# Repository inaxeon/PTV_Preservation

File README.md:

# Philips Professional Television test equipment preservation

This repository contains all of the catalogues, manuals and code dumps I have for Philips "PTV" test equipment. Presently that includes:

* PM5534 color pattern generator
* PM5544 color pattern generator
* PM5570 video test signal generator
* PM5580 TV modulator
* PM5588 TV stereo sound modulator (Zweikanalton)
* PM5631 color generator
* PM5638 component color encoder, SPG
* PM5644 color pattern generator
* PM5654 VITS generator & inserter
* PM5655 VITS generator & inserter
* PM5680 TV modulator
* PM5687 TV digital sound modulator (NICAM)
* PM5688 NICAM sound demodulator
* PM5689 NICAM monitor
* PM5690 TV multichannel converter
* PT5XXX series bits and pieces

More will be made available as I find it.

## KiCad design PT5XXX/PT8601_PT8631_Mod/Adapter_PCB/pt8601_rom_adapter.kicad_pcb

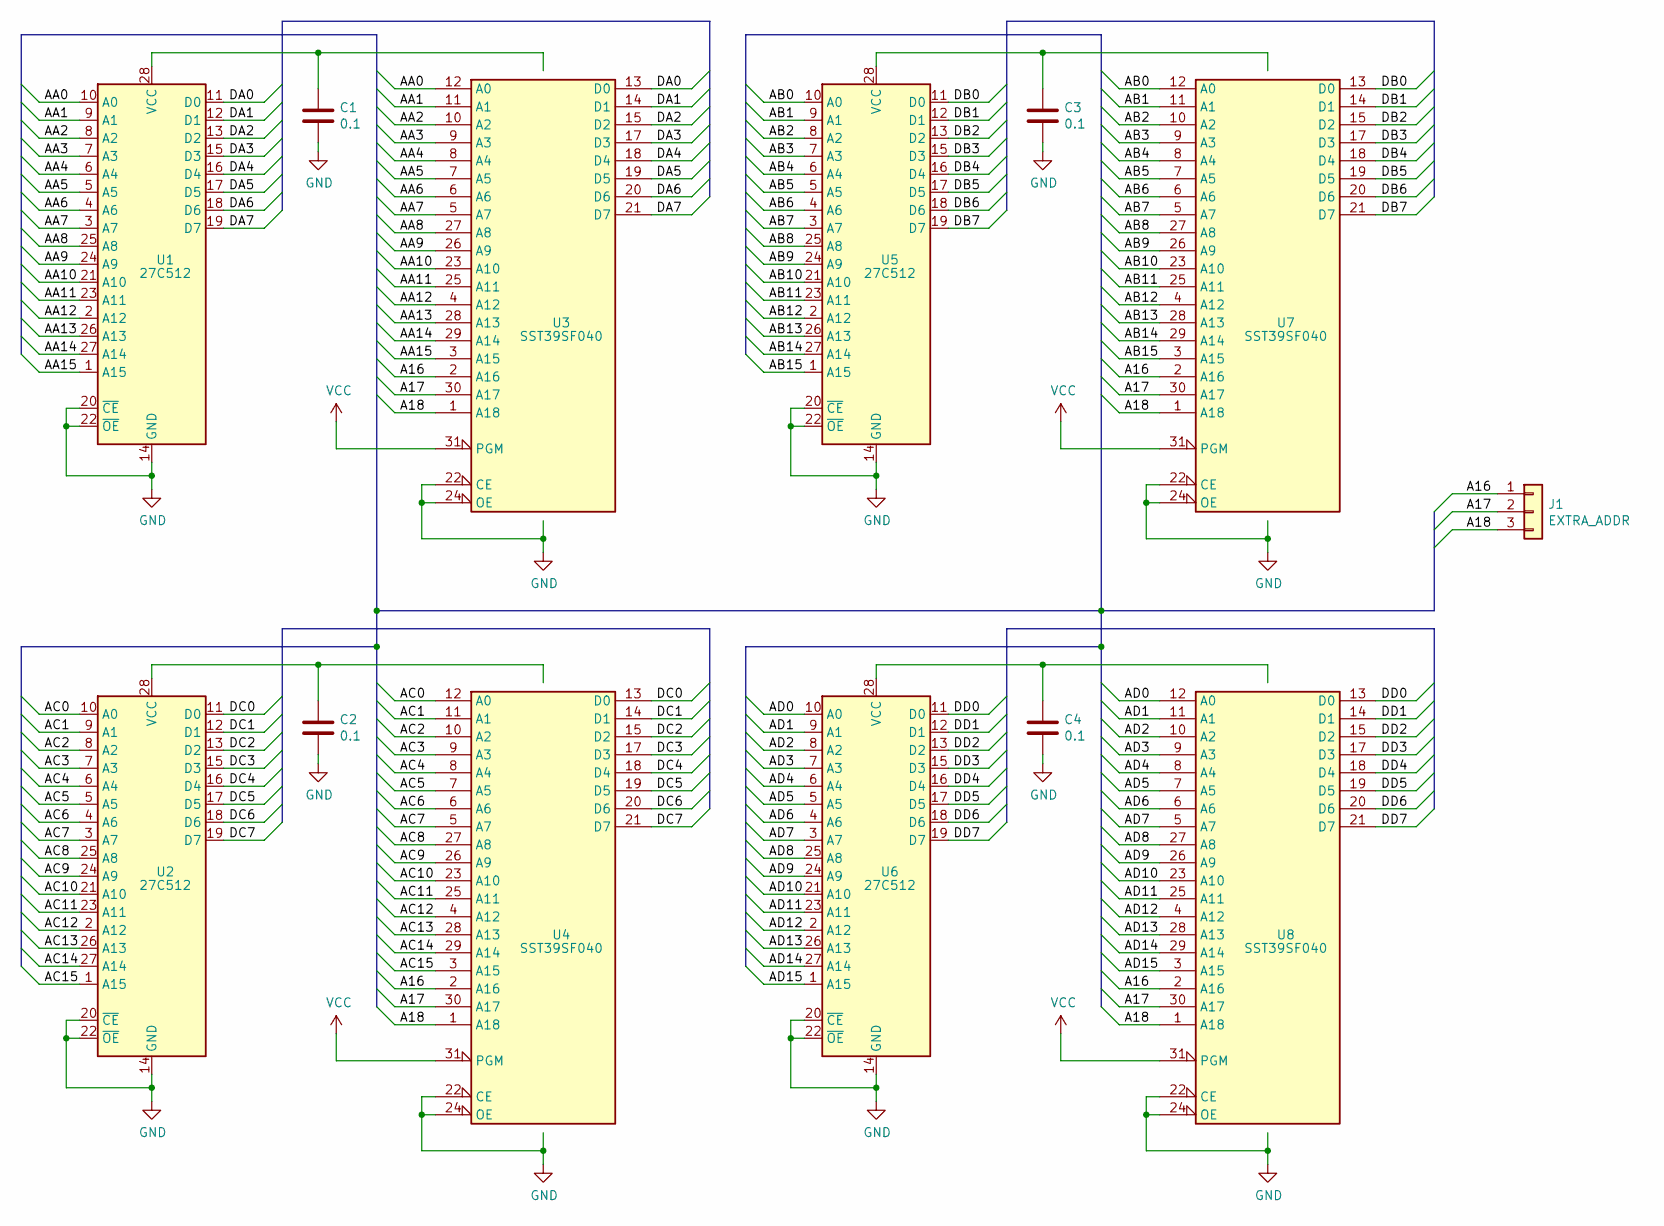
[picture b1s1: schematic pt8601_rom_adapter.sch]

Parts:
C1, C2, C3, C4: 0.1; C_1206_3216Metric
J1: EXTRA_ADDR; PinHeader_1x03_P1.27mm_Vertical
U1, U2, U5, U6: 27C512; DIP-28_W15.24mm
U3, U4, U7, U8: SST39SF040; PLCC_32_SKT

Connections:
/A16: J1.1, U3.2 (A16), U4.2 (A16), U7.2 (A16), U8.2 (A16)
/A17: J1.2, U3.30 (A17), U4.30 (A17), U7.30 (A17), U8.30 (A17)
/A18: J1.3, U3.1 (A18), U4.1 (A18), U7.1 (A18), U8.1 (A18)
/AA0: U1.10 (A0), U3.12 (A0)
/AA1: U1.9 (A1), U3.11 (A1)
/AA2: U1.8 (A2), U3.10 (A2)
/AA3: U1.7 (A3), U3.9 (A3)
/AA4: U1.6 (A4), U3.8 (A4)
/AA5: U1.5 (A5), U3.7 (A5)
/AA6: U1.4 (A6), U3.6 (A6)
/AA7: U1.3 (A7), U3.5 (A7)
/AA8: U1.25 (A8), U3.27 (A8)
/AA9: U1.24 (A9), U3.26 (A9)
/AA10: U1.21 (A10), U3.23 (A10)
/AA11: U1.23 (A11), U3.25 (A11)
/AA12: U1.2 (A12), U3.4 (A12)
/AA13: U1.26 (A13), U3.28 (A13)
/AA14: U1.27 (A14), U3.29 (A14)
/AA15: U1.1 (A15), U3.3 (A15)
/AB0: U5.10 (A0), U7.12 (A0)
/AB1: U5.9 (A1), U7.11 (A1)
/AB2: U5.8 (A2), U7.10 (A2)
/AB3: U5.7 (A3), U7.9 (A3)
/AB4: U5.6 (A4), U7.8 (A4)
/AB5: U5.5 (A5), U7.7 (A5)
/AB6: U5.4 (A6), U7.6 (A6)
/AB7: U5.3 (A7), U7.5 (A7)
/AB8: U5.25 (A8), U7.27 (A8)
/AB9: U5.24 (A9), U7.26 (A9)
/AB10: U5.21 (A10), U7.23 (A10)
/AB11: U5.23 (A11), U7.25 (A11)
/AB12: U5.2 (A12), U7.4 (A12)
/AB13: U5.26 (A13), U7.28 (A13)
/AB14: U5.27 (A14), U7.29 (A14)
/AB15: U5.1 (A15), U7.3 (A15)
/AC0: U2.10 (A0), U4.12 (A0)
/AC1: U2.9 (A1), U4.11 (A1)
/AC2: U2.8 (A2), U4.10 (A2)
/AC3: U2.7 (A3), U4.9 (A3)
/AC4: U2.6 (A4), U4.8 (A4)
/AC5: U2.5 (A5), U4.7 (A5)
/AC6: U2.4 (A6), U4.6 (A6)
/AC7: U2.3 (A7), U4.5 (A7)
/AC8: U2.25 (A8), U4.27 (A8)
/AC9: U2.24 (A9), U4.26 (A9)
/AC10: U2.21 (A10), U4.23 (A10)
/AC11: U2.23 (A11), U4.25 (A11)
/AC12: U2.2 (A12), U4.4 (A12)
/AC13: U2.26 (A13), U4.28 (A13)
/AC14: U2.27 (A14), U4.29 (A14)
/AC15: U2.1 (A15), U4.3 (A15)
/AD0: U6.10 (A0), U8.12 (A0)
/AD1: U6.9 (A1), U8.11 (A1)
/AD2: U6.8 (A2), U8.10 (A2)
/AD3: U6.7 (A3), U8.9 (A3)
/AD4: U6.6 (A4), U8.8 (A4)
/AD5: U6.5 (A5), U8.7 (A5)
/AD6: U6.4 (A6), U8.6 (A6)
/AD7: U6.3 (A7), U8.5 (A7)
/AD8: U6.25 (A8), U8.27 (A8)
/AD9: U6.24 (A9), U8.26 (A9)
/AD10: U6.21 (A10), U8.23 (A10)
/AD11: U6.23 (A11), U8.25 (A11)
/AD12: U6.2 (A12), U8.4 (A12)
/AD13: U6.26 (A13), U8.28 (A13)
/AD14: U6.27 (A14), U8.29 (A14)
/AD15: U6.1 (A15), U8.3 (A15)
/DA0: U1.11 (D0), U3.13 (D0)
/DA1: U1.12 (D1), U3.14 (D1)
/DA2: U1.13 (D2), U3.15 (D2)
/DA3: U1.15 (D3), U3.17 (D3)
/DA4: U1.16 (D4), U3.18 (D4)
/DA5: U1.17 (D5), U3.19 (D5)
/DA6: U1.18 (D6), U3.20 (D6)
/DA7: U1.19 (D7), U3.21 (D7)
/DB0: U5.11 (D0), U7.13 (D0)
/DB1: U5.12 (D1), U7.14 (D1)
/DB2: U5.13 (D2), U7.15 (D2)
/DB3: U5.15 (D3), U7.17 (D3)
/DB4: U5.16 (D4), U7.18 (D4)
/DB5: U5.17 (D5), U7.19 (D5)
/DB6: U5.18 (D6), U7.20 (D6)
/DB7: U5.19 (D7), U7.21 (D7)
/DC0: U2.11 (D0), U4.13 (D0)
/DC1: U2.12 (D1), U4.14 (D1)
/DC2: U2.13 (D2), U4.15 (D2)
/DC3: U2.15 (D3), U4.17 (D3)
/DC4: U2.16 (D4), U4.18 (D4)
/DC5: U2.17 (D5), U4.19 (D5)
/DC6: U2.18 (D6), U4.20 (D6)
/DC7: U2.19 (D7), U4.21 (D7)
/DD0: U6.11 (D0), U8.13 (D0)
/DD1: U6.12 (D1), U8.14 (D1)
/DD2: U6.13 (D2), U8.15 (D2)
/DD3: U6.15 (D3), U8.17 (D3)
/DD4: U6.16 (D4), U8.18 (D4)
/DD5: U6.17 (D5), U8.19 (D5)
/DD6: U6.18 (D6), U8.20 (D6)
/DD7: U6.19 (D7), U8.21 (D7)
GND: C1.2, C2.2, C3.2, C4.2, U1.14 (GND), U1.20 (~CE), U1.22 (~OE), U2.14 (GND), U2.20 (~CE), U2.22 (~OE), U3.16 (GND), U3.22 (CE), U3.24 (OE), U4.16 (GND), U4.22 (CE), U4.24 (OE), U5.14 (GND), U5.20 (~CE), U5.22 (~OE), U6.14 (GND), U6.20 (~CE), U6.22 (~OE), U7.16 (GND), U7.22 (CE), U7.24 (OE), U8.16 (GND), U8.22 (CE), U8.24 (OE)

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
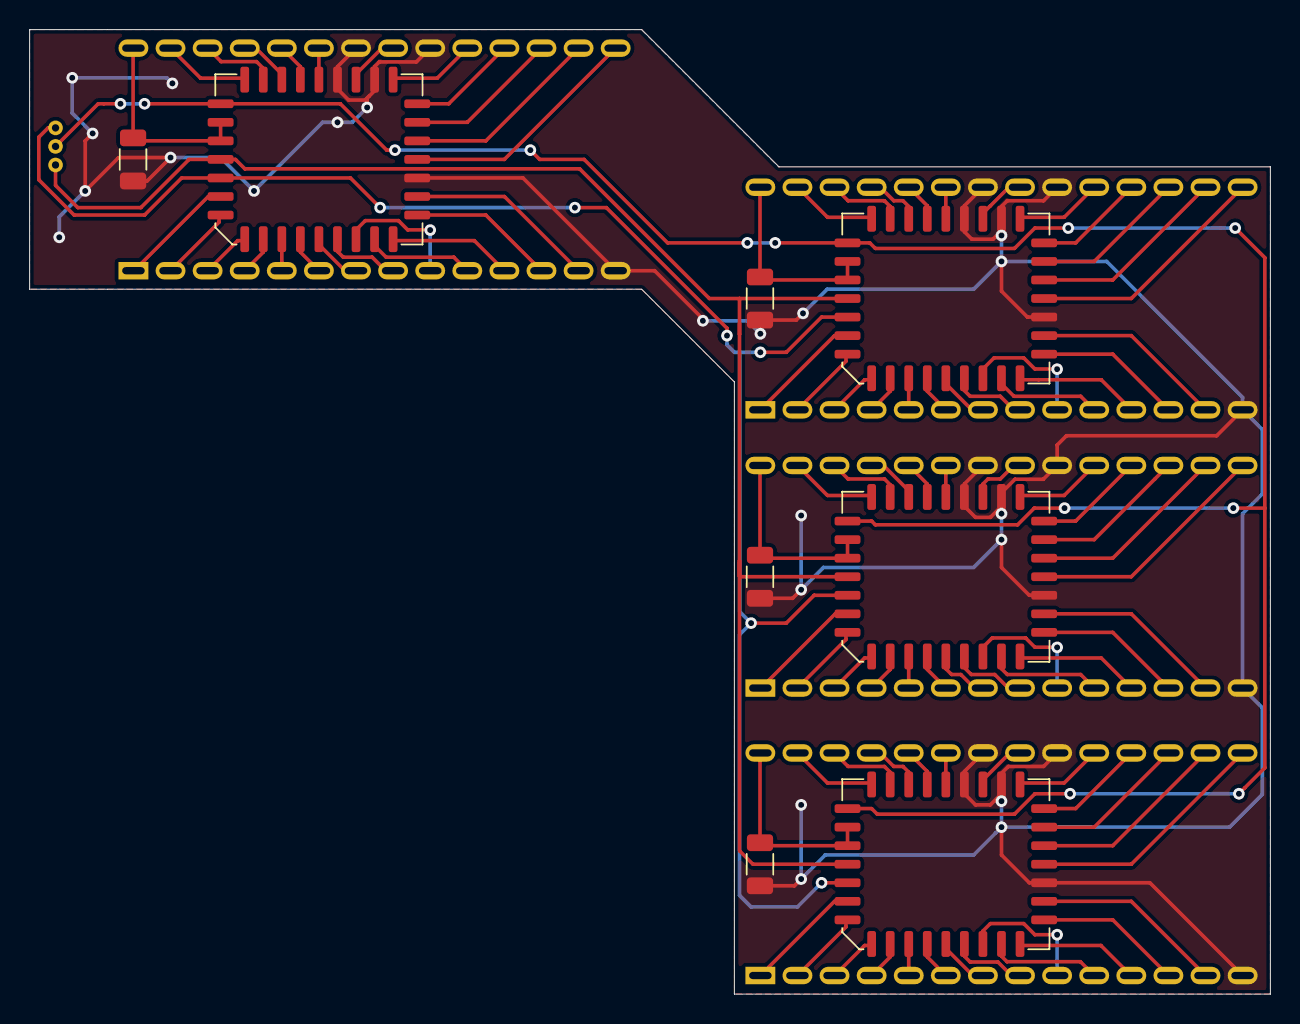
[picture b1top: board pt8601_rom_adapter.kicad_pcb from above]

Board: 2 copper layers, 85.0 x 66.0 mm, 13 parts (0 on the bottom side), 101 nets.

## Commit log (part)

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2023-03-10 More stuff added
2023-03-10 Added more schematics
2023-03-11 More schematics
2023-03-11 Added more
2023-03-11 More
2023-03-11 More added
2023-03-12 PM5638 Manual
2023-03-12 PM5688 Mainboard
2023-03-15 PM5534
2023-03-21 PM5588 catalogue pages
2023-04-19 PM5544 brochure
2023-05-20 Added PM5690 GPIB EPROM dump
2023-05-21 Add images
2023-07-01 PT8601->PT8631 modsheet added
2023-08-01 Added PT5210 DVG build, and original PT8601 code
2023-08-01 Added PT8601/902
2023-08-01 PT8601/902 modification
2023-08-02 Fix issue where artefacts are occasionally (very rarely) left on screen when changing pattern
2023-08-02 whitepace
2023-08-03 Fixed issue where card occastionally starts up in a bad state
2023-08-17 Improved PM5644 mainboard schematic. Add PM5644HD + Component version
2023-08-20 Improved logo generator schematic
2023-08-24 Added binary
2023-08-24 Comment DPRAM memory map
2023-08-24 Checksum
2023-08-25 Add U3 old version
2023-09-14 Added PM8547, move PM8546 resources to own folder
2023-10-25 Fixed V38
2023-10-31 Move folder
2023-10-31 Added OpenPM8546
2023-11-03 Fixed overvoltage condition seen occasionally when switching the clock off
2023-11-08 Implemented colour
2023-11-09 Various fixes
2023-11-11 Fine tuning / comments
2023-11-11 Added monochrome PALs
2023-11-12 Added OpenPM8546 PROMs. Handle LG Increment/query. Add more comments
2023-11-13 Add readme. Tidy up PALs.
2023-11-13 Remove extraneous zeros
2023-11-24 Swap logos
2023-12-10 PM5655 stuff
2023-12-22 Added 4:3 support + various fixes found while trying to get it working in the PM5644L
2023-12-22 Tidy up PALs. Added P22V10 builds
2024-01-04 Add what we have so far of PM5644/85 001.1
2024-01-16 Added image of rear generator board
2024-01-16 Add sync schematic
2024-01-16 Fixed page 2
2024-01-17 Added V47
2024-01-21 Added 525 line version
2024-01-22 Last of initial 525 line implementation
2024-01-23 Improved build process
2024-01-25 Update PM5655
2024-01-25 Added PROMs
2024-01-25 Add layouts
2024-01-25 Add sync/power board
2024-01-25 Add vectors
2024-01-25 Add new generator
2024-01-25 Added version
2024-01-25 Add layout
2024-01-25 PM5689
2024-01-25 PM5689 images + dumps
2024-01-28 Fix issue occasionally seen when starting 525 line build
2024-02-13 PM5534 options
2024-02-13 Rename
2024-02-13 Add circle EPROM
2024-02-19 Add PM5655G/915
2024-02-20 Add PM5534 manual
2024-02-26 Add original PM5544 manual
2024-03-06 Add G/921 dumps / images
2024-03-12 Add front panel PROM
2024-03-12 Add PM5570 operators manual
2024-04-03 Add PM5570 full manual
2024-04-04 More manuals
2024-04-04 Improved PM5688 schematics
2024-04-07 Improved QPSK schematics
2024-04-07 Add U3 layout
2024-04-08 Improve PM5644 service info
2024-04-16 Remove unused code
2024-04-28 Add U5X
2024-05-01 Upgrade PT8601/902 to full character set
2024-05-05 Updated docs
2024-06-08 PM5652M
2024-07-01 Add PM5644 manual chapter 3 scan
2024-07-01 Add George Hersee letter
2024-07-13 Re-do
2024-07-13 Added resources from BECG
2024-10-09 Added PM5644G/924 Rev 2
2025-01-19 Add PM5644/85 manual
2025-02-20 Add 1986 full catalogue
2025-02-28 Add PM5640 spec sheet
2025-03-17 Add PM5565 manual
2025-03-25 PM5640A service manual
2025-05-21 Add PM5631 manual
2025-08-21 PM8547/20
2025-08-21 RS232 interface schematic
2025-09-04 Add PM8546 dumps
2025-09-04 Add PM5644G90
2025-10-05 More stuff for PM5644 interface modules
2025-10-06 Add PM5644 Commander
2025-10-21 fixes
2025-10-30 Added improved PCF84C00T adapter board
2025-10-30 Added DXF of PM8547/20 rear plate
2025-10-30 Tidy up / add docs
2025-12-21 Add image of assembled board
2025-12-24 Added OpenPM8546 code which is (more) compatible with original PALs and character PROMs
2026-04-13 Added slightly better manual scan
2026-06-19 Changed to correct dump
